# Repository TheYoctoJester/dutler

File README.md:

# DUTler 🎩

[-brightgreen.svg)](CONTRIBUTING.md)

> **A bench butler for your Device Under Test.**
> Sponsored by [Northern.tech](https://northern.tech) as part of the
> [Mender.io](https://mender.io) community engagement.

> ⚠️ **Experimental.** DUTler is provided **"AS IS", without warranties or conditions of any
> kind, and without any support**. It's an experiment, not a supported product — don't rely on
> it for anything critical.

DUTler is open-source firmware that turns a ~$4 **Raspberry Pi Pico (RP2040)** into a small,
always-there sidecar for **OS-level integration work** — building, flashing, updating, and
*recovering* embedded-Linux devices. It targets the loop you actually live in when doing
**Yocto** builds and **Mender** over-the-air updates: flash an image, watch it boot, and — when
one wedges the board mid-update — get it back **without walking over to the bench**.

Over a single USB cable, DUTler gives you the two things that loop always needs:

- a **serial console** to the device — a genuine USB-to-UART bridge with the host baud rate
  mirrored onto the hardware UART; and
- **power and control lines** — a relay to switch DUT power, plus low-side MOSFET drivers to
  assert the board's boot-mode/strapping and reset pins, so you can power-cycle it and drop it
  into a recovery/bootloader mode when an update leaves it unresponsive;

plus a separate **firmware debug log**, so DUTler's own diagnostics never pollute the device
console.

It's built for Mender + Yocto bring-up and **CI / hardware-in-the-loop** rigs, but nothing about
it is Mender-specific — it's a generic console-plus-power companion for *any* board under test.
The name is *DUT* (Device Under Test) + *butler*: it quietly attends your board, serves up the
console, and flips the power when asked.

The firmware makes a stock Pico enumerate as **three USB serial ports**:

| USB port | Purpose |
|----------|---------|
| **CDC0 — "UART Bridge"** | Transparent USB ↔ hardware-UART bridge (a real USB-serial adapter; host baud rate is mirrored onto the UART). |
| **CDC1 — "Control"** | Newline-terminated commands to switch the DUT control outputs — a power relay plus MOSFET strap/reset drivers. |
| **CDC2 — "Debug Log"** | Read-only firmware log stream (open it to start receiving; output is dropped when nobody is listening). |

They enumerate as three serial ports, in this order — **bridge, control, debug log**:

- **Linux:** `/dev/ttyACM0`, `/dev/ttyACM1`, `/dev/ttyACM2`. For access without `sudo`, add
  yourself to the `dialout` group once: `sudo usermod -aG dialout "$USER"` (then re-login).
  Open a port with `tio`, `minicom`, or `screen`.
- **macOS:** `/dev/cu.usbmodem*` — `…1` (bridge), `…3` (control), `…5` (debug log). Open with
  `screen`.

The examples below use the macOS `cu.usbmodem*` names; on Linux substitute the matching
`/dev/ttyACM*`.

## Requirements

**Host (build machine): macOS or Linux.**

- **CMake ≥ 3.13**, **Ninja**, **picotool**, and the **Arm GNU bare-metal toolchain**
  (`arm-none-eabi-gcc` — developed against *14.2.Rel1*).
  - macOS: `brew install cmake ninja picotool`, plus the Arm toolchain (download the
    `arm-gnu-toolchain-*-arm-none-eabi` for darwin, start [here](https://gitlab.arm.com/tooling/gnu-toolchains-for-arm) and download e.g. this [tarball](https://gitlab.arm.com/api/v4/projects/tooling%2Fgnu-toolchains-for-arm/packages/generic/gnu-toolchain/14.2.rel1/arm-gnu-toolchain-14.2.rel1-darwin-arm64-arm-none-eabi.pkg) and unpack it).
  - Linux: your distro's `cmake`, `ninja-build`, `picotool` (or build it), plus the Arm GNU
    toolchain (distro package or the official tarball).
- **Raspberry Pi Pico SDK 2.2.0** with submodules (it pulls in TinyUSB).
- **Python 3** — only for the host-side helper scripts in `tools/` (optional).

Put the SDK and toolchain **next to this repo** (siblings of the `DUTler/` directory) and `env.sh`
finds them automatically — or export `PICO_SDK_PATH` / `PICO_TOOLCHAIN_PATH` / `picotool_DIR`
yourself (env.sh honors anything already set, which is how CI pins its own paths).

**Target:** a stock **Raspberry Pi Pico (RP2040)** (`PICO_BOARD=pico`, the default), a
**Pico 2 (RP2350)** (`PICO_BOARD=pico2`), or a **Pico 2 W (RP2350)** (`PICO_BOARD=pico2_w`), plus
a USB cable. The firmware adapts the flash layout to the board's actual size at runtime; on the
wireless Pico 2 W the activity LED hangs off the CYW43 chip and is simply skipped (no wireless stack
is pulled in), whereas the non-wireless Pico 2 keeps its GP25 LED heartbeat. A single jumper wire
between **GP0 and GP1** is handy for the bridge loopback self-test.

## Quick start

Once the requirements are in place:

```sh
# fetch the SDK as a sibling of this repo (one-time)
git -C .. clone --branch 2.2.0 https://github.com/raspberrypi/pico-sdk.git
git -C ../pico-sdk submodule update --init

# build -> build/dutler.uf2
source env.sh
cmake -S . -B build -G Ninja \
  -DPICO_SDK_PATH="$PICO_SDK_PATH" \
  -DPICO_TOOLCHAIN_PATH="$PICO_TOOLCHAIN_PATH" \
  -Dpicotool_DIR="$picotool_DIR"
# …add -DPICO_BOARD=pico2 (or pico2_w for the wireless Pico 2) to build for the RP2350 instead.
cmake --build build

# flash: hold BOOTSEL while plugging in the Pico, then
./flash.sh                              # or drag build/dutler.uf2 onto the RPI-RP2 drive

# use it: three USB serial ports appear
ls /dev/cu.usbmodem*                    # macOS: …1 bridge, …3 control, …5 debug
# ls /dev/ttyACM*                       # Linux:  ttyACM0/1/2 = bridge/control/debug
screen /dev/cu.usbmodemXXXX1 115200     # the DUT serial console (Linux: tio/minicom/screen on ttyACM0)
#   …then open the control port and type 'help' for the output/strap/reset commands
```

See **Build**, **Flash** and **Test** below for the details, and **Wiring** for pin assignments.

## Wiring (firmware defaults — `include/config.h`)

These are the firmware's pin assignments. They match the **v1 HAT** in [`hardware/`](hardware/)
one-for-one; on a bare Pico, wire your own driver modules to the same pins.

| Function | Pin | On the v1 HAT |
|----------|-----|---------------|
| Bridge UART TX | GP0 → device RX | header J2 |
| Bridge UART RX | GP1 ← device TX | header J2 |
| Control out 1 — MOSFET | GP2 — low-side strap/boot-mode or reset line | 2N7000 → J1 |
| Control out 2 — MOSFET | GP3 — low-side strap/boot-mode or reset line | 2N7000 → J3 |
| Control out 3 — power relay | GP4 — switch DUT power | ULN2003 → relay → J4 |
| Control out 4 — spare | GP5 — firmware-defined, no driver on v1 | — |
| Activity LED | GP25 (on-board) | — |
| GND | any GND pin — **share ground with the DUT and any relay/MOSFET board** | J2 / J1 / J3 |

All control outputs are 3.3 V logic, **active-high, and OFF at boot**. In firmware they're just
generic switched GPIOs (all driven via the `out`/`name` commands); their *intended* roles are:

- **Outs 1 & 2 → low-side MOSFET gates** — to pull the DUT's strapping/boot-mode and reset lines
  (e.g. force USB/serial download mode, then toggle reset). The MOSFET does the level shift and
  the pull; the GPIO only drives its gate. Match the DUT's logic level and share ground.
- **Out 3 → a power relay** — to cut/restore DUT power. Use a relay **module** with its own
  driver/opto stage; don't switch a coil straight off a GPIO.
- **Out 4 → spare** — a free GPIO with no driver on the v1 HAT; wire your own if you need a fourth.

Tip: alias the outputs to their jobs once and drive them by name —
`name 1 bootmode`, `name 2 reset`, `name 3 power`, then `power off` / `bootmode on` / `reset on`.
Count, pins and polarity live in `include/config.h` (`OUT_*`); `OUT_ACTIVE_LOW 1` flips sense.

## Build

```sh
source env.sh                # sets PICO_SDK_PATH, toolchain, picotool (self-contained)
cmake -S . -B build -G Ninja \
  -DPICO_SDK_PATH="$PICO_SDK_PATH" \
  -DPICO_TOOLCHAIN_PATH="$PICO_TOOLCHAIN_PATH" \
  -Dpicotool_DIR="$picotool_DIR"     # first time only
cmake --build build                  # -> build/dutler.uf2
```

## Flash

```sh
./flash.sh
```

When the adapter is already running, `flash.sh` reboots it into the bootloader
automatically (no button) by sending the control port's `bootsel` command, then loads the new
image. You can also trigger the reset yourself:

- send `bootsel` to the control port, **or**
- open the **debug** port at **1200 baud** (the classic USB-serial "1200-baud touch";
  compile-time `ENABLE_BAUD_TOUCH_RESET` in `config.h`, on by default), **or**
- `python3 tools/reset_bootsel.py`

**First flash / wedged board:** hold the **BOOTSEL** button while plugging in (mounts as
`RPI-RP2`), then run `./flash.sh` or drag `build/dutler.uf2` onto the drive.

> The 1200-baud reset is wired to the *debug* port only — the bridge port stays free to use
> any real baud rate (including 1200).

## Test

### On hardware

After flashing, **three** devices appear: `ls /dev/tty.usbmodem*` (bridge / control / debug log).

- **Bridge loopback:** jumper **GP0↔GP1**, open the *UART Bridge* port and echo:
  ```sh
  screen /dev/tty.usbmodemXXXX 115200     # type chars -> should echo back
  ```
  (Ctrl-A then K to quit `screen`.) Changing baud still works — it's pushed to the UART. The
  control port's `selftest` command checks GP0↔GP1 continuity for you.
- **Control outputs:** open the *Control* port and send commands:
  ```
  help
  status
  out 1 on
  out 1 off
  name 2 fan
  fan toggle
  ```

### Unit tests (host)

The pure logic — CRC-32, integer parsing, and the settings record codec — has off-target unit
tests that build with the **native** compiler (no Pico, no SDK):

```sh
cmake -S tests -B build-tests
cmake --build build-tests
ctest --test-dir build-tests --output-on-failure
```

CI runs these on every push and pull request.

## Control commands

Open the **Control** port (CDC1) and type `help` — the firmware prints the authoritative,
always-current command list, so this README doesn't try to mirror it. In brief:

> **Response protocol (for scripting).** Every command's reply is CRLF lines ending with a single
> **status line**: `OK`, or `ERR <message>`. Any data (e.g. `baud 115200`) comes before it. So a
> script sends `cmd\r\n` and **reads lines until one equals `OK` or starts with `ERR `** — no
> timeout guessing, and an empty result (e.g. `get kv` with nothing stored) still returns `OK`.
> In interactive-shell mode the terminator is shown in human form (`ok` / `error:`, colourised).

- **`out <id> on|off|toggle`** drives an output by number (`1..`) or configured name, with an
  `<id> on|off|toggle` shorthand (e.g. `pump on`).
- Settings and device properties are a small **key/value store**: **`set <key> <value>`** writes and
  **`get [<key>]`** reads (with no key, `get` dumps all the built-in settings/properties below; the
  user `kv` store is listed separately via `get kv`). The keys are:
  - **`baud`** / **`format`** (e.g. `8N1`) — bridge UART defaults (effective after `save` + reboot).
  - **`echo`** (`on|off`) — control-port local echo (off by default; effective immediately, handy
    for raw terminals that don't echo locally).
  - **`shell`** (`on|off`) — interactive-shell mode (off by default); see *Interactive shell* below.
  - **`outname <n>`** (`<alias|clear>`) — label output `n` (usable as the shorthand verb above).
  - **`dutname`** (`<str|clear>`) — a human/DUT-oriented label (`[A-Za-z0-9._-]`, ≤ 23 chars). It
    goes into the USB product string, so the `/dev/serial/by-id/` path becomes
    `usb-theyoctojester_DUTler-<name>_<serial>-if0N` — handy for telling several DUTlers apart on
    one host. Applied immediately via a live USB re-enumeration (open handles on that DUTler drop
    and must be reopened); persisted by `save`.
  - **`serial`** — read-only device property; `get serial` prints the Pico's hardware unique ID
    (the same value used as the USB `iSerial`). `set serial` is rejected.
  - **`version`** — read-only; `get version` prints the firmware version. `set version` is rejected.
  - **`kv <key>`** — a user key/value store for arbitrary strings (asset tag, rack location, DUT
    notes…), kept in its own flash area separate from the built-in settings. `set kv <key> <value>`
    stores (the value is the rest of the line, so spaces are allowed); `set kv <key> clear` deletes;
    `get kv <key>` reads one; `get kv` lists all. Keys are `[A-Za-z0-9._-]` (≤ 31 chars, and not
    `OK`/`ERR`, which are reserved for the response terminator), values ≤ 111 chars. Like the other
    settings it stages until `save`.
- **`save`** persists the settings to flash; **`status`** shows the outputs plus a quick summary.
- **`selftest`** (GP0↔GP1 loopback), **`factory-reset confirm`**, **`help`** (the command list),
  **`bootsel`** (reboot into the USB bootloader), and **`reset`** (warm reboot into the
  application, e.g. to clear an occasional UART lockup) round it out.

### Interactive shell

`set shell on` turns the Control port into a readline-style shell: a `dutler> ` prompt, in-line
editing (Left/Right/Home/End, Ctrl-A/E, backspace/Delete), Up/Down command **history**, **Ctrl-R**
reverse search, Ctrl-U/K/W kill + Ctrl-Y yank, **Tab** completion of commands/keys/values/output
names, and coloured replies (errors red, `ok` green). The firmware drives the whole terminal, so
the host just needs a raw, VT100-style terminal (`picocom`, `screen`, …). Note that **scrollback is
a terminal feature**, not the DUTler's — use `screen`/`tmux` if you want it (`picocom` has none);
history, by contrast, lives in the DUTler.

Shell mode is **off by default** so the promptless, un-echoed line protocol stays clean for scripts
and CI; persist your choice with `save`. A DUTler left in shell mode will feed prompt/echo/colour to
a scripted `printf | cat` driver, so keep it off for automation.

## Persistent settings

Output **names**, the **bridge boot UART config**, the **control-port echo** flag, the
**device name**, and the **interactive-shell** flag are stored in flash. `set …` commands
change them in RAM (shown as "unsaved changes" in `status`); `save` writes them. They survive
power cycles *and* normal firmware reflashes (the UF2 only overwrites the program region, not
the settings sectors).

Storage uses an **A/B (ping-pong) scheme** across the last two 4 KB sectors: each record
carries a monotonic sequence number, `save` writes the *inactive* slot and verifies it before
it counts, and load picks the valid slot with the highest sequence. The active slot is never
erased, so a **failed or power-interrupted save cannot lose the last good config** — load just
falls back to the older slot (the half-written one fails its CRC). A blank/garbage pair falls
back to safe defaults. The record is **versioned**; `src/core/settings.c` documents the append-only
evolution rules and migrates older formats in place on first boot (single-slot v1 records are
upgraded to A/B, pre-device-name v2 records to v3, and pre-shell-flag v3 records to v4, preserving
the existing settings).

**Outputs themselves always boot OFF** — their state is deliberately not persisted, so a power
blip can never silently re-energize a load. Implemented in `src/core/settings.c`
(struct, CRC32, flash erase/program) — note flash writes briefly mask interrupts (a few ms),
so avoid `save` in the middle of heavy bridge traffic.

## Watchdog

A hardware watchdog (`WATCHDOG_TIMEOUT_MS` in `config.h`, default 2 s) is fed every main-loop
iteration, so a wedged loop (e.g. a hung USB stack) reboots and recovers automatically. The
`save` path feeds it just before the interrupts-masked flash erase, which is the longest
blocking section. At boot the firmware records whether the reset was a real watchdog timeout
(via `watchdog_enable_caused_reboot()`, which ignores deliberate `bootsel`/reflash reboots)
and `status` reports it. Outputs always come up OFF after any reset.

## Design notes / non-goals

- **No UART flow control — intentional, not missing.** The bridge is a 3-wire link
  (TX/RX/GND): no hardware RTS/CTS and no software XON/XOFF. This is a deliberate scope
  decision. Backpressure exists where it matters — USB→UART is non-blocking and NAKs the host
  when the staging buffer fills — and the only lossy path (UART→USB ring overflow when the host
  stops reading) is **reported** on the debug port rather than prevented. Use matched baud
  rates and don't firehose the bridge from a flow-controlled peer. Please don't "add the missing
  flow control": it's a choice. If a future use case genuinely needs it, wire RTS/CTS pins and
  call `uart_set_hw_flow()` in `bridge.c` — but that's a new feature, not a fix.

## Debug log

Firmware logs go to the **Debug Log** port (CDC2). Watch them with:

```sh
screen /dev/cu.usbmodemXXXX5 115200      # or: python3 tools/debug_capture.py
```

The firmware also logs **`bridge: RX overflow ...`** here (rate-limited) if the UART-to-USB
ring ever drops bytes because the host stopped draining — so silent data loss becomes visible.

Add your own with `dbg_printf("...")` (declared in `src/platform/debug.h`). Output is only sent while a
host has the port open, so calls are cheap when unused. **Do not call `dbg_printf` from an
interrupt handler** (it touches the USB TX FIFO shared with the main loop).

> USB VID/PID in `config.h` are pid.codes **test** IDs — replace before any distribution.

## Contributing

Contributions are welcome — see [`CONTRIBUTING.md`](CONTRIBUTING.md). Contributions are accepted
under a DCO sign-off (`git commit -s`) — no CLA. Please follow the
[Code of Conduct](CODE_OF_CONDUCT.md), and report security issues privately per
[`SECURITY.md`](SECURITY.md).

## License

Copyright © 2026 Northern.tech AS.

The firmware is licensed under the **Apache License, Version 2.0** — see [`LICENSE`](LICENSE) for
the full text and [`NOTICE`](NOTICE) for attribution. Every source file carries the
[SPDX](https://spdx.dev) identifier `Apache-2.0`.

The software is distributed on an **"AS IS" basis, without warranties or conditions of any kind,
and without support**.

- **Hardware** design files in [`hardware/`](hardware/) are licensed under **CERN-OHL-P-2.0** (the
  permissive CERN Open Hardware Licence) — see [`hardware/LICENSE`](hardware/LICENSE) and
  `hardware/README.md`.
- **Documentation** is offered under **CC-BY-4.0**.

Third-party components keep their own licenses and are *not* relicensed (Pico SDK, TinyUSB,
newlib, libgcc, …) — see [`THIRD_PARTY.md`](THIRD_PARTY.md).

## Acknowledgements

DUTler is **sponsored by [Northern.tech](https://northern.tech) as part of the
[Mender.io](https://mender.io) community engagement** — thank you for backing open tooling for
the embedded-Linux community. Thanks also to the Raspberry Pi Pico SDK and TinyUSB projects,
which do the heavy USB lifting.

The majority of the code in this repository was generated with
[Claude Code](https://claude.com/claude-code), under human direction and review.

> "Mender", "Northern.tech", and the Mender moose are trademarks of Northern.tech AS. They are
> used here only to describe the project's purpose and the integration workflow it serves.

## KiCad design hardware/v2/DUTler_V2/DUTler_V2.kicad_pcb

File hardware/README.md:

# DUTler — Hardware

Open-source hardware for the DUTler carrier/HAT: a small board that breaks a Raspberry Pi Pico
out into bench-friendly connectors for driving a device under test —

- the **bridge UART** (GP0/GP1) on a labelled 3-pin header;
- two **low-side MOSFET drivers** for the DUT's strapping/boot-mode and reset lines;
- one **power relay** (driven via a ULN2003, with flyback protection) to switch DUT power; and
- the **gate pull-downs** that hold every output OFF at power-on.

The firmware also runs fine on a bare Pico with jumper wires — this board just makes the wiring
permanent and bench-friendly. See the top-level [`README.md`](../README.md) *Wiring* section for
the pin map (it is kept in sync with this board).

## Contents

```
hardware/
├── README.md                 # this file
├── LICENSE                   # CERN-OHL-P-2.0 (see "License" below)
└── v1/
    └── DUTler_v1/            # KiCad 9 project — the v1 design
        ├── DUTler_v1.kicad_pro   # project
        ├── DUTler_v1.kicad_sch   # schematic
        ├── DUTler_v1.kicad_pcb   # board layout
        └── BOM.md                # bill of materials + assembly notes
```

Only the KiCad **design source** is tracked. Generated outputs (Gerbers/drill, `*.kicad_prl`
local settings, `*-backups/`, the local-history dir) are `.gitignore`d — regenerate them from
the `.kicad_pcb` when you send the board to fabrication.

## Status

**v1 — first iteration, not yet fabricated or bench-verified.** The schematic and layout are
complete enough to review and route; treat footprints, the relay coil-voltage variant, and the
connector pinouts as **provisional** until a board has been built and tested.

## Opening the design

Open `v1/DUTler_v1/DUTler_v1.kicad_pro` in **KiCad 9** (or newer). Older KiCad will refuse the
file format (schematic `version 20260306`, PCB `version 20260206`).

## What it drives (v1)

| Pico | Net | Part | Connector |
|------|-----|------|-----------|
| GP0 / GP1 | bridge UART TX/RX | — | J2 (TX, RX, GND) |
| GP2 | out 1 | 2N7000 MOSFET (Q1), low-side | J1 |
| GP3 | out 2 | 2N7000 MOSFET (Q2), low-side | J3 |
| GP4 | out 3 | ULN2003 → relay coil (K1) | J4 (NC, NO, COM) |
| GP5 | out 4 | *(firmware spare — no driver on v1)* | — |

The MOSFET gates have 220 Ω series resistors (R2/R3) and 10 kΩ gate-to-source pull-downs
(R1/R4), so both MOSFETs sit OFF at power-on. The relay idles de-energized (ULN2003 input low),
and its coil free-wheels through the ULN2003's internal diode (COM tied to the coil supply).

J4 breaks out the relay contacts as **pin 1 = NC, pin 2 = NO, pin 3 = COM** (Finder terminals
12 / 14 / 11). Energizing the relay (`out 3 on`, active-high) connects **COM → NO**, so route the
DUT supply through **COM (pin 3) and NO (pin 2)** if you want `on` to mean *powered*.

> **Relay coil voltage:** K1's coil is wired to **VBUS (5 V)**. Fit the 5 V FINDER 34.51
> (`34.51.7.005.0010`) — a 12 V/24 V part will not actuate. See the BOM notes in
> [`v1/DUTler_v1/BOM.md`](v1/DUTler_v1/BOM.md).

## License

Copyright © 2026 Northern.tech AS.

The hardware design files in this directory are licensed under **CERN-OHL-P-2.0** — see
[`LICENSE`](LICENSE). This is the **permissive** CERN Open Hardware Licence: you may use, study,
modify, make and distribute products based on these files, without a reciprocal obligation to
release your modifications. The design is provided **"AS IS", without warranties of any kind**.

> KiCad's S-expression files carry no per-file comment headers, so the SPDX identifier
> (`CERN-OHL-P-2.0`) is recorded here and in the project rather than inline. The firmware in the
> parent repo is licensed under **Apache-2.0** (see [`../LICENSE`](../LICENSE)).

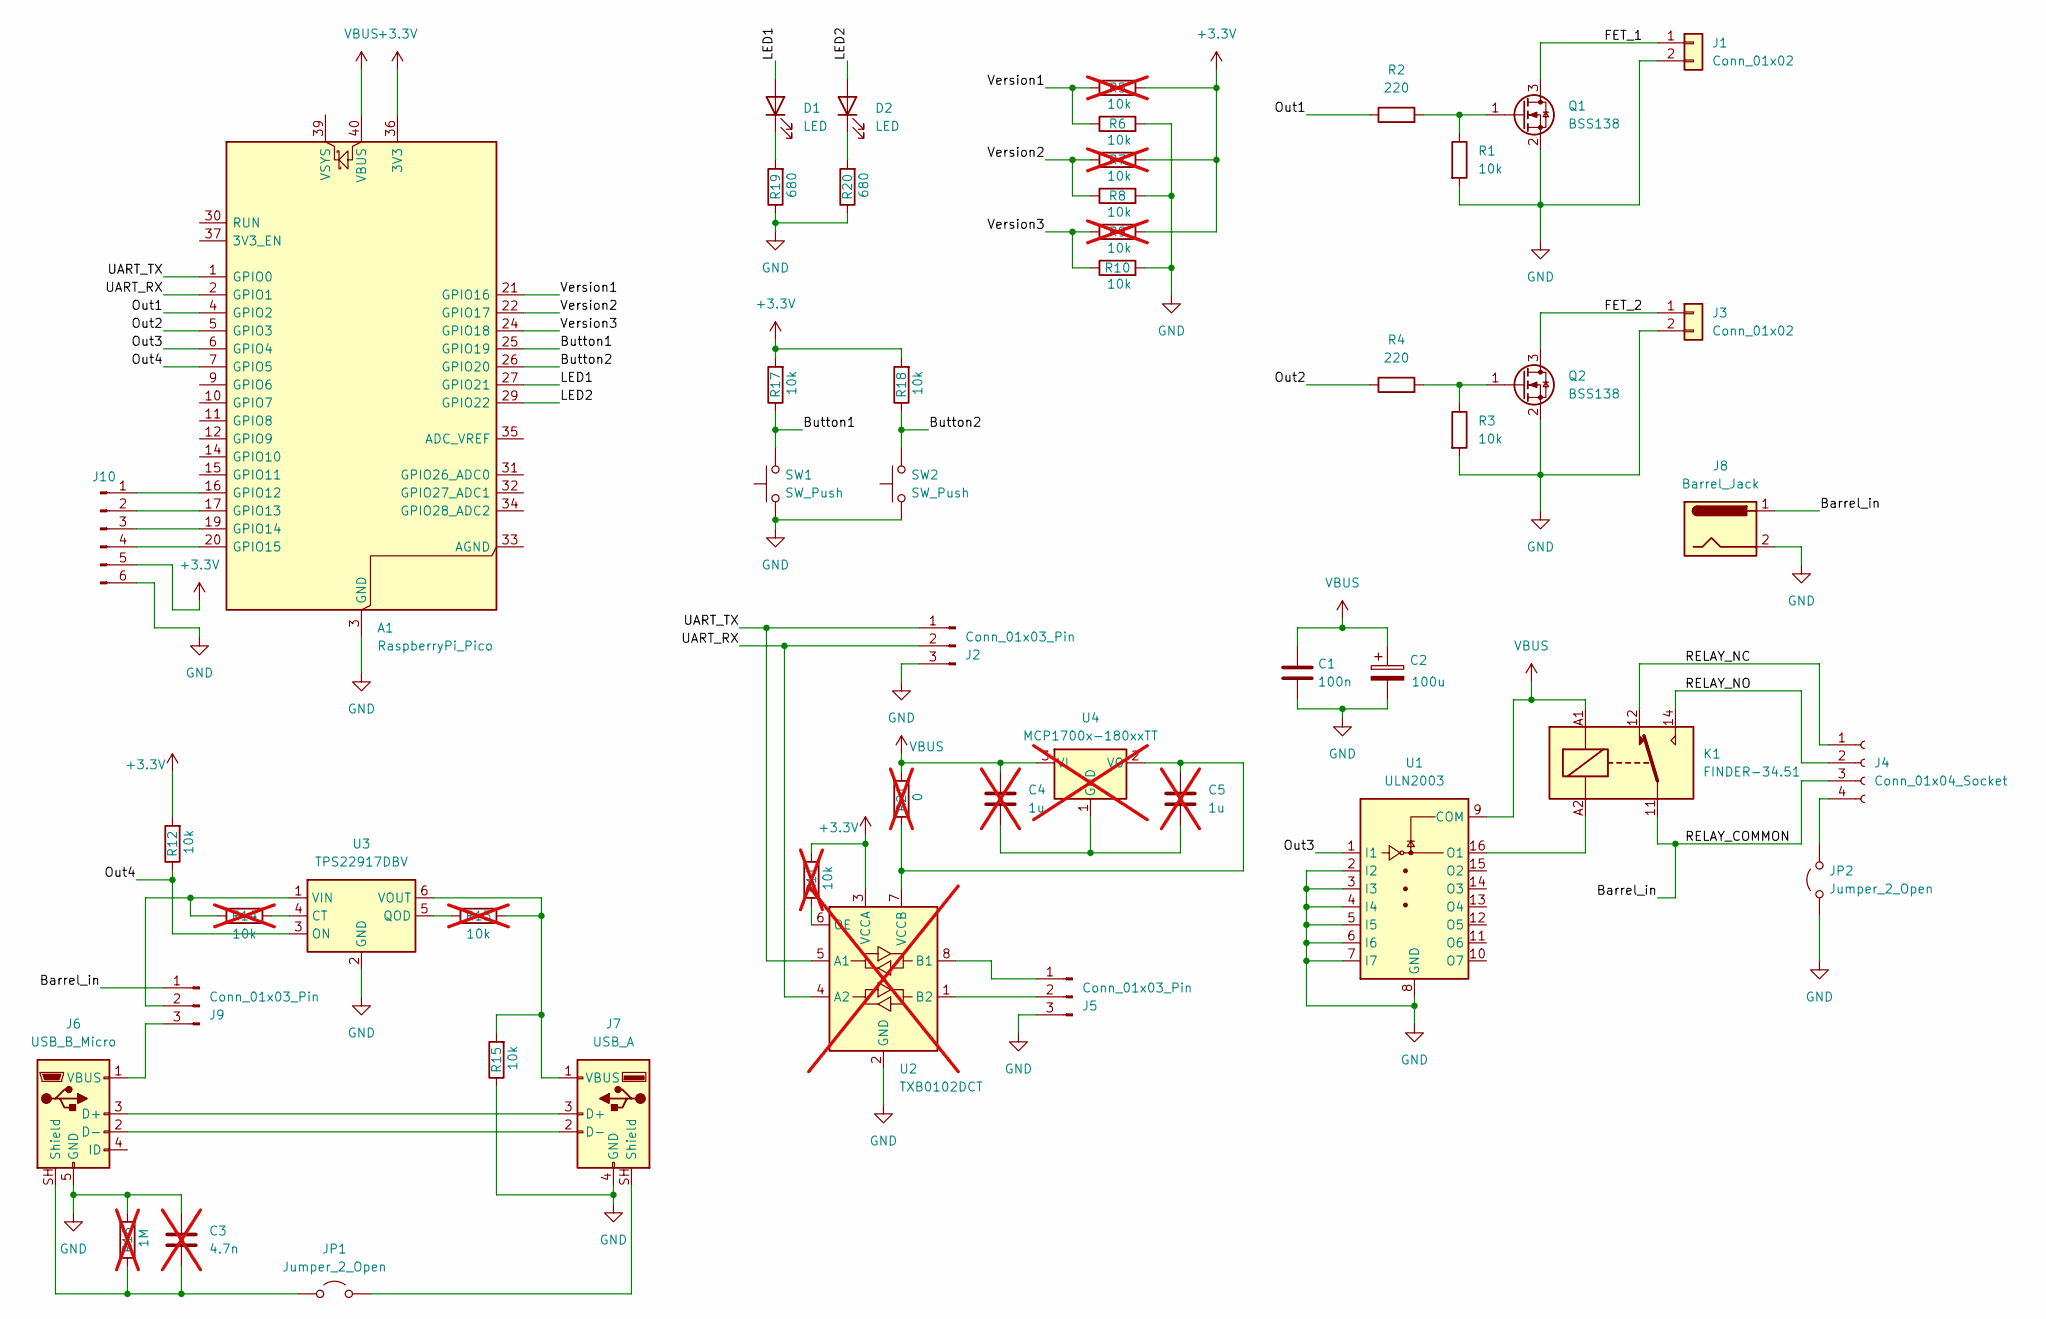
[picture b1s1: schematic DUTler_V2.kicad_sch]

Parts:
A1: RaspberryPi_Pico; RaspberryPi_Pico_Common_Unspecified
C1: 100n; C_Rect_L7.0mm_W2.5mm_P5.00mm
C2: 100u; C_Radial_D6.3mm_H11.0mm_P2.50mm
C3: 4.7n; C_0805_2012Metric_Pad1.18x1.45mm_HandSolder; not fitted
C4, C5: 1u; C_0805_2012Metric_Pad1.18x1.45mm_HandSolder; not fitted
D1, D2: LED; LED_0805_2012Metric_Pad1.15x1.40mm_HandSolder
J1, J3: Conn_01x02; PinHeader_1x02_P2.54mm_Vertical
J2, J5, J9: Conn_01x03_Pin; PinHeader_1x03_P2.54mm_Vertical
J4: Conn_01x04_Socket; TerminalBlock_Phoenix_MKDS-1,5-4-5.08_1x04_P5.08mm_Horizont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
J6: USB_B_Micro; USB_Micro-B_Wuerth_629105150521
J7: USB_A; USB_A_Wuerth_614004134726_Horizontal
J8: Barrel_Jack; BarrelJack_Wuerth_6941xx301002
J10: Conn_01x06_Pin; PinHeader_1x06_P2.54mm_Vertical
JP1, JP2: Jumper_2_Open; PinHeader_1x02_P2.54mm_Vertical
K1: FINDER-34.51; Relay_SPDT_Finder_34.51_Vertical
Q1, Q2: BSS138; SOT-23
R1, R3, R6, R8, R10, R12, R15, R17, R18: 10k; R_0603_1608Metric_Pad0.98x0.95mm_HandSolder
R2, R4: 220; R_0603_1608Metric_Pad0.98x0.95mm_HandSolder
R5, R7, R9, R11, R13, R14: 10k; R_0603_1608Metric_Pad0.98x0.95mm_HandSolder; not fitted
R16: 1M; R_0603_1608Metric_Pad0.98x0.95mm_HandSolder; not fitted
R19, R20: 680; R_0603_1608Metric_Pad0.98x0.95mm_HandSolder
R21: 0; R_0603_1608Metric_Pad0.98x0.95mm_HandSolder; not fitted
SW1, SW2: SW_Push; SW_SPST_PTS645Sx43SMTR92
U1: ULN2003; SOIC-16_3.9x9.9mm_P1.27mm
U2: TXB0102DCT; TSSOP-8_3x3mm_P0.65mm; not fitted
U3: TPS22917DBV; SOT-23-6
U4: MCP1700x-180xxTT; SOT-23; not fitted

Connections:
+3.3V: A1.36 (3V3), J10.5, R5.2, R7.2, R9.2, R11.2, R12.2, R17.2, R18.2, U2.3 (VCCA)
/Barrel_in: J4.3, J8.1, J9.1, K1.11
/Button1: A1.25 (GPIO19), R17.1, SW1.2
/Button2: A1.26 (GPIO20), R18.1, SW2.2
/FET_1: J1.1, Q1.3 (D)
/FET_2: J3.1, Q2.3 (D)
/LED1: A1.27 (GPIO21), D1.2 (A)
/LED2: A1.29 (GPIO22), D2.2 (A)
/Out1: A1.4 (GPIO2), R2.1
/Out2: A1.5 (GPIO3), R4.1
/Out3: A1.6 (GPIO4), U1.1 (I1)
/Out4: A1.7 (GPIO5), R12.1, U3.3 (ON)
/RELAY_NC: J4.1, K1.12
/RELAY_NO: J4.2, K1.14
/UART_RX: A1.2 (GPIO1), J2.2, U2.4 (A2)
/UART_TX: A1.1 (GPIO0), J2.1, U2.5 (A1)
/Version1: A1.21 (GPIO16), R5.1, R6.1
/Version2: A1.22 (GPIO17), R7.1, R8.1
/Version3: A1.24 (GPIO18), R9.1, R10.1
GND: A1.3 (GND), A1.8 (GND), A1.13 (GND), A1.18 (GND), A1.23 (GND), A1.28 (GND), A1.38 (GND), C1.2, C2.2, C3.1, J1.2, J2.3, J3.2, J5.3, J6.5 (GND), J7.4 (GND), J8.2, J10.6, JP2.1 (A), Q1.2 (S), Q2.2 (S), R1.2, R3.2, R6.2, R8.2, R10.2, R15.1, R16.2, R19.1, R20.1, SW1.1, SW2.1, U1.2 (I2), U1.3 (I3), U1.4 (I4), U1.5 (I5), U1.6 (I6), U1.7 (I7), U1.8 (GND), U2.2 (GND), U3.2 (GND)
unnamed: A1.16 (GPIO12), J10.1
unnamed: A1.17 (GPIO13), J10.2
unnamed: A1.19 (GPIO14), J10.3
unnamed: A1.20 (GPIO15), J10.4
unnamed: D1.1 (K), R19.2
unnamed: D2.1 (K), R20.2
unnamed: J4.4, JP2.2 (B)
unnamed: J5.1, U2.8 (B1)
unnamed: J5.2, U2.1 (B2)
unnamed: J6.3 (D+), J7.3 (D+)
unnamed: J6.2 (D-), J7.2 (D-)
unnamed: C3.2, J6.SH (Shield), JP1.1 (A), R16.1
unnamed: J6.1 (VBUS), J9.3
unnamed: J7.SH (Shield), JP1.2 (B)
unnamed: J7.1 (VBUS), R13.1, R15.2, U3.6 (VOUT)
unnamed: J9.2, R14.2, U3.1 (VIN)
unnamed: Q1.1 (G), R1.1, R2.2
unnamed: Q2.1 (G), R3.1, R4.2
unnamed: K1.A2, U1.16 (O1)
unnamed: R11.1, U2.6 (OE)
unnamed: C5.1, R21.1, U2.7 (VCCB), U4.2 (VO)
unnamed: R14.1, U3.4 (CT)
unnamed: R13.2, U3.5 (QOD)
unnamed: C4.2, C5.2, U4.1 (GND)
VBUS: A1.40 (VBUS), C1.1, C2.1, C4.1, K1.A1, R21.2, U1.9 (COM), U4.3 (VI)

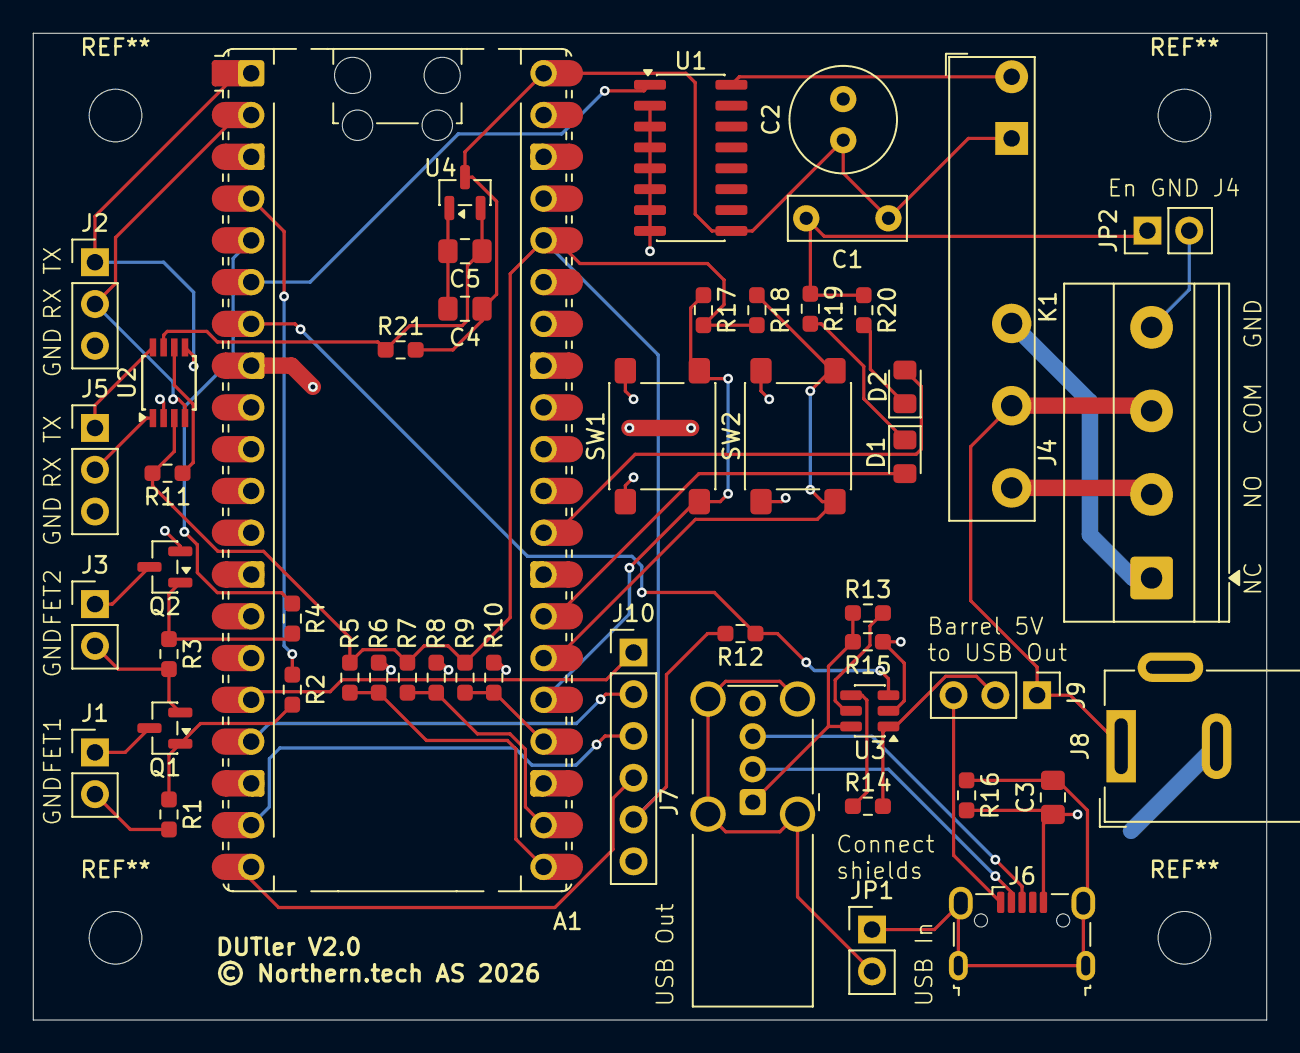
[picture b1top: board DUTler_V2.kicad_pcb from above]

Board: 2 copper layers, 75.0 x 60.0 mm, 50 parts (0 on the bottom side), 45 nets.

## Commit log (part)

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2026-06-21 ci: bump actions/checkout from 4.3.1 to 7.0.0
    Bumps [actions/checkout](https://github.com/actions/checkout) from 4.3.1 to 7.0.0.
    - [Release notes](https://github.com/actions/checkout/releases)
    - [Changelog](https://github.com/actions/checkout/blob/main/CHANGELOG.md)
    - [Commits](https://github.com/actions/checkout/compare/34e114876b0b11c390a56381ad16ebd13914f8d5...9c091bb21b7c1c1d1991bb908d89e4e9dddfe3e0)
    ---
    updated-dependencies:
2026-06-21 ci: bump actions/upload-artifact from 4.6.2 to 7.0.1
    Bumps [actions/upload-artifact](https://github.com/actions/upload-artifact) from 4.6.2 to 7.0.1.
    - [Release notes](https://github.com/actions/upload-artifact/releases)
    - [Commits](https://github.com/actions/upload-artifact/compare/ea165f8d65b6e75b540449e92b4886f43607fa02...043fb46d1a93c77aae656e7c1c64a875d1fc6a0a)
    ---
    updated-dependencies:
    - dependency-name: actions/upload-artifact
2026-06-21 ci: bump actions/setup-python from 5.6.0 to 6.2.0
    Bumps [actions/setup-python](https://github.com/actions/setup-python) from 5.6.0 to 6.2.0.
    - [Release notes](https://github.com/actions/setup-python/releases)
    - [Commits](https://github.com/actions/setup-python/compare/a26af69be951a213d495a4c3e4e4022e16d87065...a309ff8b426b58ec0e2a45f0f869d46889d02405)
    ---
    updated-dependencies:
    - dependency-name: actions/setup-python

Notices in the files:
README.md:
License: Apache-2.0
hardware/v2/DUTler_V2/DUTler_V2.kicad_pcb:
© Northern.tech AS 2026
